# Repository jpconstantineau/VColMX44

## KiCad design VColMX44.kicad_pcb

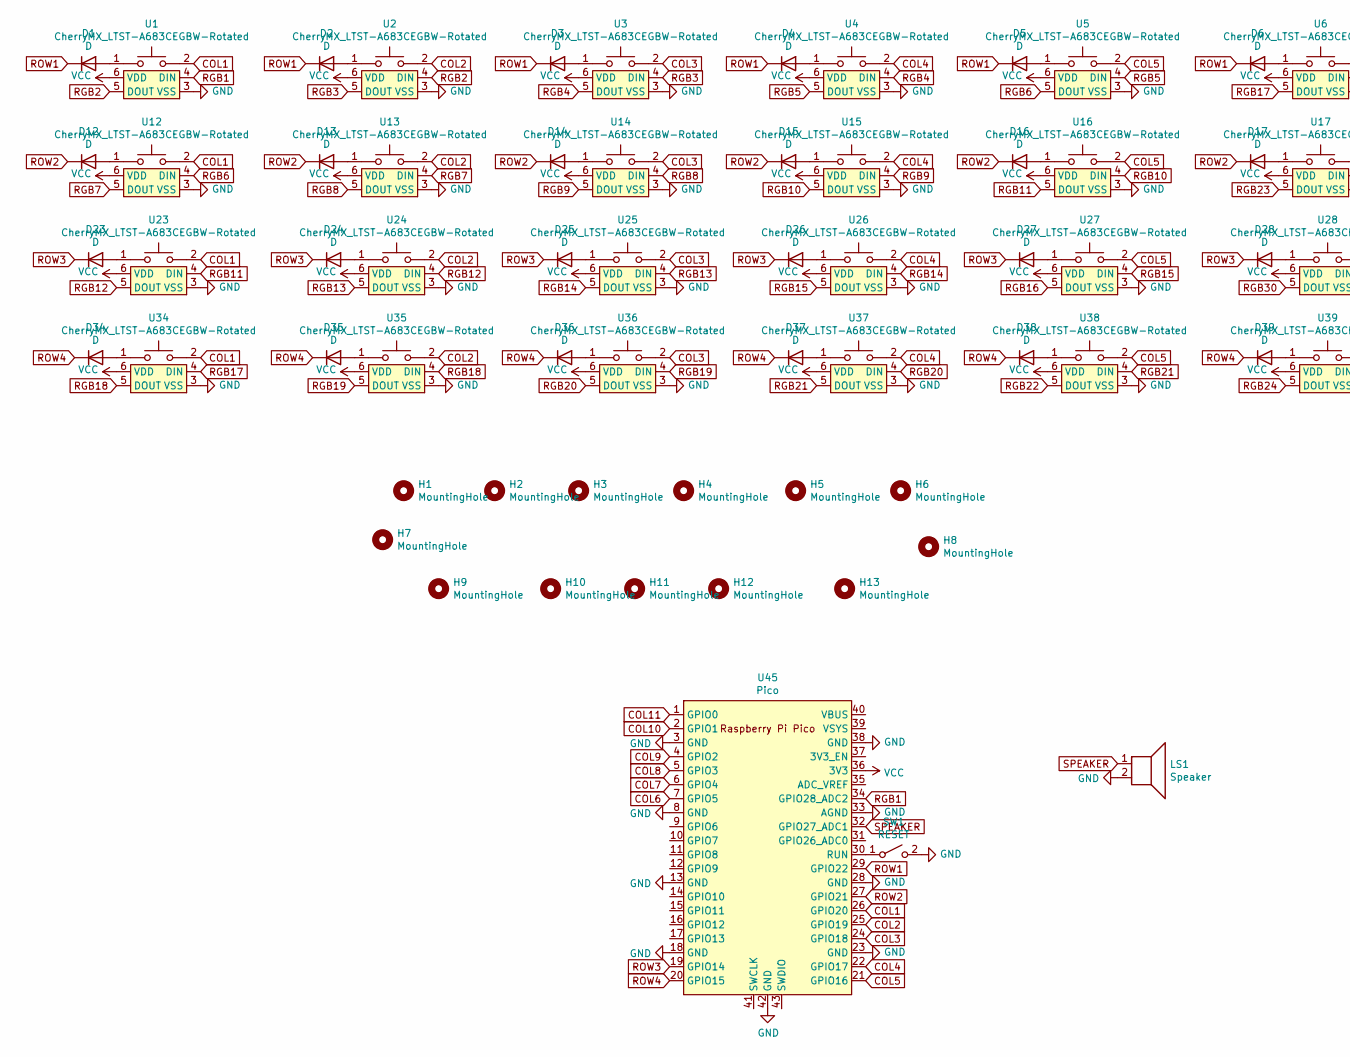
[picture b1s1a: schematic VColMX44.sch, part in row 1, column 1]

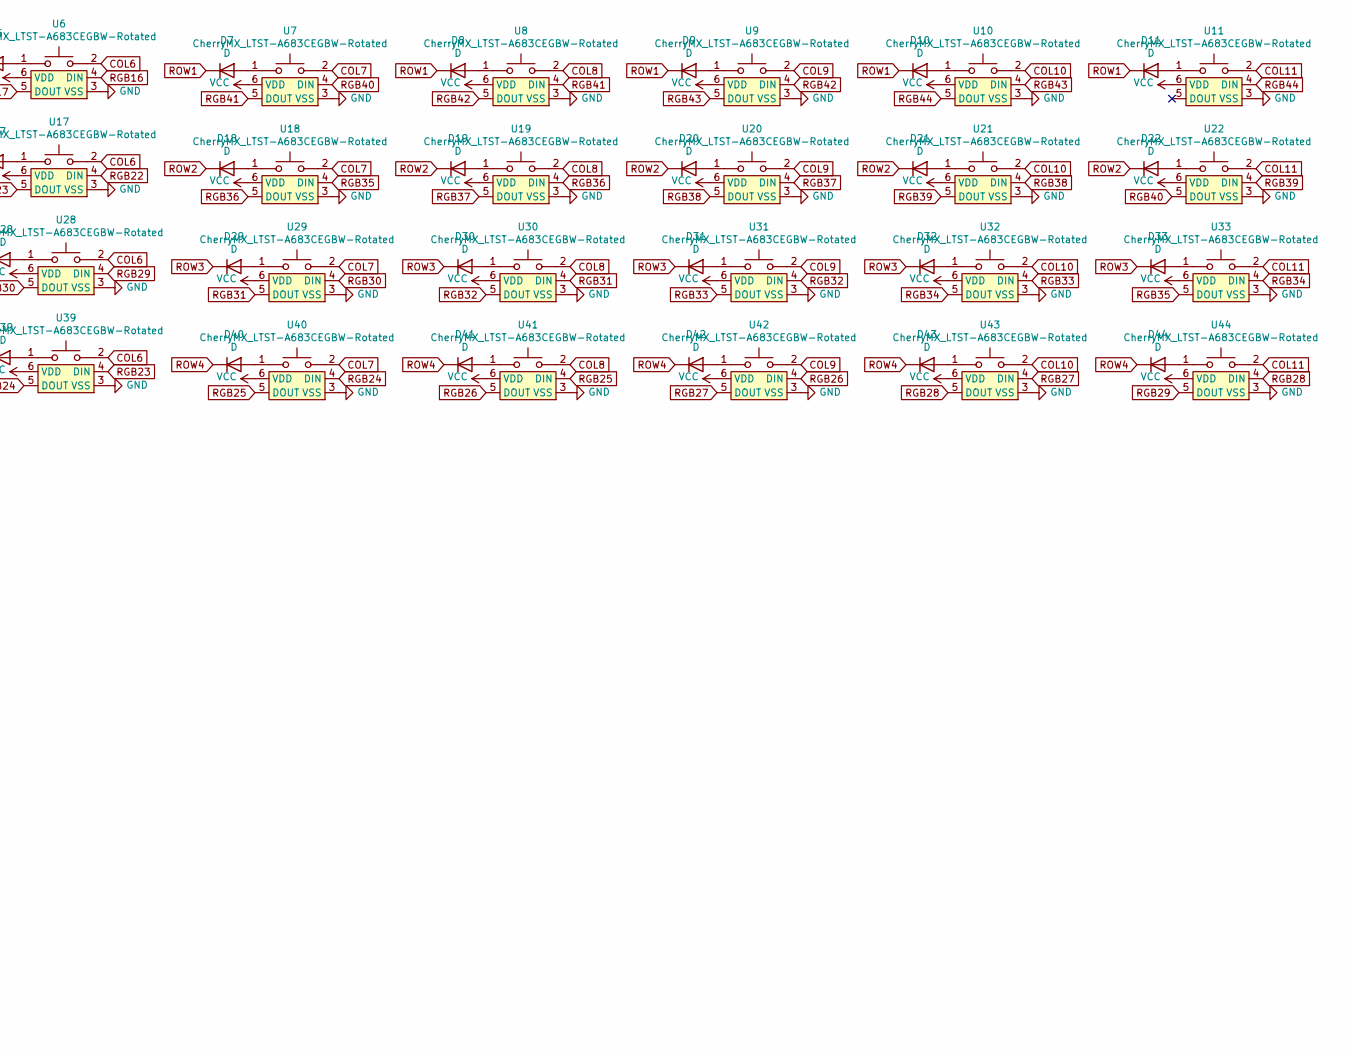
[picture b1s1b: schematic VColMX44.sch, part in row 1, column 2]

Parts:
D1, D2, D3, D4, D5, D6, D7, D8, D9, D10, D11, D12, D13, D14, D15, D16, D17, D18, D19, D20, D21, D22, D23, D24, D25, D26, D27, D28, D29, D30, D31, D32, D33, D34, D35, D36, D37, D38, D39, D40, D41, D42, D43, D44: D; D_SOD-123
H1, H2, H3, H4, H5, H6, H7, H8, H9, H10, H11, H12, H13: MountingHole; MountingHole_2.2mm_M2_DIN965
LS1: Speaker; Buzzer_Mallory_AST1109MLTRQ
SW1: RESET; SW_SPST_TL3342
U1, U2, U3, U4, U5, U6, U7, U8, U9, U10, U11, U12, U13, U14, U15, U16, U17, U18, U19, U20, U21, U22, U23, U24, U25, U26, U27, U28, U29, U30, U31, U32, U33, U34, U35, U36, U37, U38, U39, U40, U41, U42, U43, U44: CherryMX_LTST-A683CEGBW-Rotated; CherryMX_1.00u_PCB_KailhSocket_LTST-A683CEGBW-Rotated
U45: Pico; RPi_Pico_SMD

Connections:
COL1: U1.2, U12.2, U23.2, U34.2, U45.26 (GPIO20)
COL2: U2.2, U13.2, U24.2, U35.2, U45.25 (GPIO19)
COL3: U3.2, U14.2, U25.2, U36.2, U45.24 (GPIO18)
COL4: U4.2, U15.2, U26.2, U37.2, U45.22 (GPIO17)
COL5: U5.2, U16.2, U27.2, U38.2, U45.21 (GPIO16)
COL6: U6.2, U17.2, U28.2, U39.2, U45.7 (GPIO5)
COL7: U7.2, U18.2, U29.2, U40.2, U45.6 (GPIO4)
COL8: U8.2, U19.2, U30.2, U41.2, U45.5 (GPIO3)
COL9: U9.2, U20.2, U31.2, U42.2, U45.4 (GPIO2)
COL10: U10.2, U21.2, U32.2, U43.2, U45.2 (GPIO1)
COL11: U11.2, U22.2, U33.2, U44.2, U45.1 (GPIO0)
GND: LS1.2, SW1.2 (B), U1.3 (VSS), U2.3 (VSS), U3.3 (VSS), U4.3 (VSS), U5.3 (VSS), U6.3 (VSS), U7.3 (VSS), U8.3 (VSS), U9.3 (VSS), U10.3 (VSS), U11.3 (VSS), U12.3 (VSS), U13.3 (VSS), U14.3 (VSS), U15.3 (VSS), U16.3 (VSS), U17.3 (VSS), U18.3 (VSS), U19.3 (VSS), U20.3 (VSS), U21.3 (VSS), U22.3 (VSS), U23.3 (VSS), U24.3 (VSS), U25.3 (VSS), U26.3 (VSS), U27.3 (VSS), U28.3 (VSS), U29.3 (VSS), U30.3 (VSS), U31.3 (VSS), U32.3 (VSS), U33.3 (VSS), U34.3 (VSS), U35.3 (VSS), U36.3 (VSS), U37.3 (VSS), U38.3 (VSS), U39.3 (VSS), U40.3 (VSS), U41.3 (VSS), U42.3 (VSS), U43.3 (VSS), U44.3 (VSS), U45.3 (GND), U45.8 (GND), U45.13 (GND), U45.18 (GND), U45.23 (GND), U45.28 (GND), U45.33 (AGND), U45.38 (GND), U45.42 (GND)
unnamed: D1.2 (A), U1.1
unnamed: D2.2 (A), U2.1
unnamed: D3.2 (A), U3.1
unnamed: D4.2 (A), U4.1
unnamed: D5.2 (A), U5.1
unnamed: D6.2 (A), U6.1
unnamed: D7.2 (A), U7.1
unnamed: D8.2 (A), U8.1
unnamed: D9.2 (A), U9.1
unnamed: D10.2 (A), U10.1
unnamed: D11.2 (A), U11.1
unnamed: D12.2 (A), U12.1
unnamed: D13.2 (A), U13.1
unnamed: D14.2 (A), U14.1
unnamed: D15.2 (A), U15.1
unnamed: D16.2 (A), U16.1
unnamed: D17.2 (A), U17.1
unnamed: D18.2 (A), U18.1
unnamed: D19.2 (A), U19.1
unnamed: D20.2 (A), U20.1
unnamed: D21.2 (A), U21.1
unnamed: D22.2 (A), U22.1
unnamed: D23.2 (A), U23.1
unnamed: D24.2 (A), U24.1
unnamed: D25.2 (A), U25.1
unnamed: D26.2 (A), U26.1
unnamed: D27.2 (A), U27.1
unnamed: D28.2 (A), U28.1
unnamed: D29.2 (A), U29.1
unnamed: D30.2 (A), U30.1
unnamed: D31.2 (A), U31.1
unnamed: D32.2 (A), U32.1
unnamed: D33.2 (A), U33.1
unnamed: D34.2 (A), U34.1
unnamed: D35.2 (A), U35.1
unnamed: D36.2 (A), U36.1
unnamed: D37.2 (A), U37.1
unnamed: D38.2 (A), U38.1
unnamed: D39.2 (A), U39.1
unnamed: D40.2 (A), U40.1
unnamed: D41.2 (A), U41.1
unnamed: D42.2 (A), U42.1
unnamed: D43.2 (A), U43.1
unnamed: D44.2 (A), U44.1
unnamed: SW1.1 (A), U45.30 (RUN)
RGB1: U1.4 (DIN), U45.34 (GPIO28_ADC2)
RGB2: U1.5 (DOUT), U2.4 (DIN)
RGB3: U2.5 (DOUT), U3.4 (DIN)
RGB4: U3.5 (DOUT), U4.4 (DIN)
RGB5: U4.5 (DOUT), U5.4 (DIN)
RGB6: U5.5 (DOUT), U12.4 (DIN)
RGB7: U12.5 (DOUT), U13.4 (DIN)
RGB8: U13.5 (DOUT), U14.4 (DIN)
RGB9: U14.5 (DOUT), U15.4 (DIN)
RGB10: U15.5 (DOUT), U16.4 (DIN)
RGB11: U16.5 (DOUT), U23.4 (DIN)
RGB12: U23.5 (DOUT), U24.4 (DIN)
RGB13: U24.5 (DOUT), U25.4 (DIN)
RGB14: U25.5 (DOUT), U26.4 (DIN)
RGB15: U26.5 (DOUT), U27.4 (DIN)
RGB16: U6.4 (DIN), U27.5 (DOUT)
RGB17: U6.5 (DOUT), U34.4 (DIN)
RGB18: U34.5 (DOUT), U35.4 (DIN)
RGB19: U35.5 (DOUT), U36.4 (DIN)
RGB20: U36.5 (DOUT), U37.4 (DIN)
RGB21: U37.5 (DOUT), U38.4 (DIN)
RGB22: U17.4 (DIN), U38.5 (DOUT)
RGB23: U17.5 (DOUT), U39.4 (DIN)
RGB24: U39.5 (DOUT), U40.4 (DIN)
RGB25: U40.5 (DOUT), U41.4 (DIN)
RGB26: U41.5 (DOUT), U42.4 (DIN)
RGB27: U42.5 (DOUT), U43.4 (DIN)
RGB28: U43.5 (DOUT), U44.4 (DIN)
RGB29: U28.4 (DIN), U44.5 (DOUT)
RGB30: U28.5 (DOUT), U29.4 (DIN)
RGB31: U29.5 (DOUT), U30.4 (DIN)
RGB32: U30.5 (DOUT), U31.4 (DIN)
RGB33: U31.5 (DOUT), U32.4 (DIN)
RGB34: U32.5 (DOUT), U33.4 (DIN)
RGB35: U18.4 (DIN), U33.5 (DOUT)
RGB36: U18.5 (DOUT), U19.4 (DIN)
RGB37: U19.5 (DOUT), U20.4 (DIN)
RGB38: U20.5 (DOUT), U21.4 (DIN)
RGB39: U21.5 (DOUT), U22.4 (DIN)
RGB40: U7.4 (DIN), U22.5 (DOUT)
RGB41: U7.5 (DOUT), U8.4 (DIN)
RGB42: U8.5 (DOUT), U9.4 (DIN)
RGB43: U9.5 (DOUT), U10.4 (DIN)
RGB44: U10.5 (DOUT), U11.4 (DIN)
ROW1: D1.1 (K), D2.1 (K), D3.1 (K), D4.1 (K), D5.1 (K), D6.1 (K), D7.1 (K), D8.1 (K), D9.1 (K), D10.1 (K), D11.1 (K), U45.29 (GPIO22)
ROW2: D12.1 (K), D13.1 (K), D14.1 (K), D15.1 (K), D16.1 (K), D17.1 (K), D18.1 (K), D19.1 (K), D20.1 (K), D21.1 (K), D22.1 (K), U45.27 (GPIO21)
ROW3: D23.1 (K), D24.1 (K), D25.1 (K), D26.1 (K), D27.1 (K), D28.1 (K), D29.1 (K), D30.1 (K), D31.1 (K), D32.1 (K), D33.1 (K), U45.19 (GPIO14)
ROW4: D34.1 (K), D35.1 (K), D36.1 (K), D37.1 (K), D38.1 (K), D39.1 (K), D40.1 (K), D41.1 (K), D42.1 (K), D43.1 (K), D44.1 (K), U45.20 (GPIO15)
SPEAKER: LS1.1, U45.32 (GPIO27_ADC1)
VCC: U1.6 (VDD), U2.6 (VDD), U3.6 (VDD), U4.6 (VDD), U5.6 (VDD), U6.6 (VDD), U7.6 (VDD), U8.6 (VDD), U9.6 (VDD), U10.6 (VDD), U11.6 (VDD), U12.6 (VDD), U13.6 (VDD), U14.6 (VDD), U15.6 (VDD), U16.6 (VDD), U17.6 (VDD), U18.6 (VDD), U19.6 (VDD), U20.6 (VDD), U21.6 (VDD), U22.6 (VDD), U23.6 (VDD), U24.6 (VDD), U25.6 (VDD), U26.6 (VDD), U27.6 (VDD), U28.6 (VDD), U29.6 (VDD), U30.6 (VDD), U31.6 (VDD), U32.6 (VDD), U33.6 (VDD), U34.6 (VDD), U35.6 (VDD), U36.6 (VDD), U37.6 (VDD), U38.6 (VDD), U39.6 (VDD), U40.6 (VDD), U41.6 (VDD), U42.6 (VDD), U43.6 (VDD), U44.6 (VDD), U45.36 (3V3)

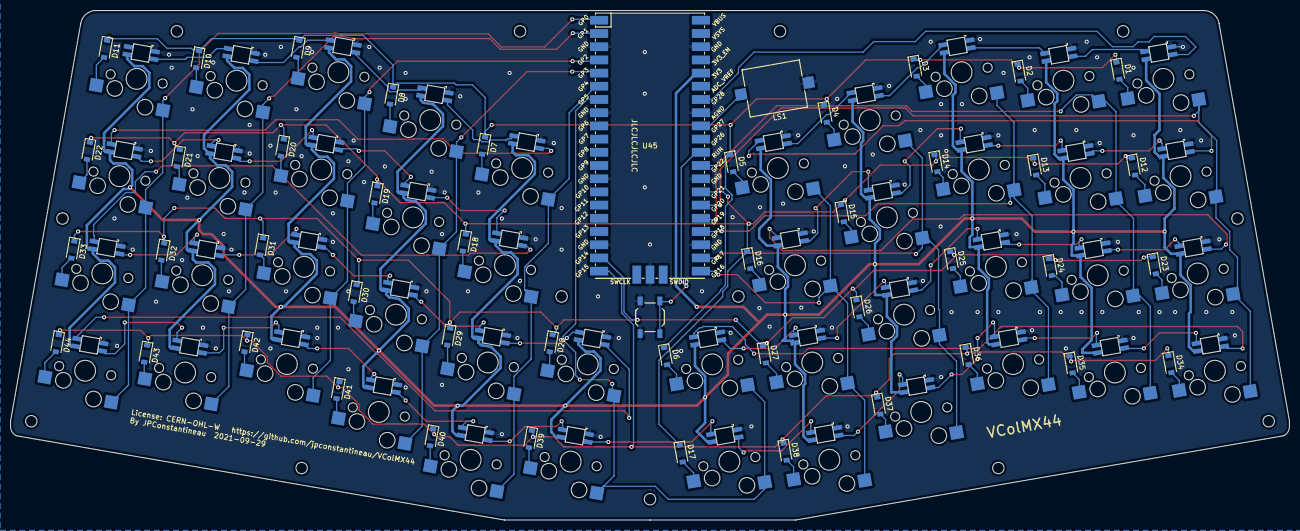
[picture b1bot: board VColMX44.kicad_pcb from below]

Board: 2 copper layers, 246.0 x 98.0 mm, 104 parts (47 on the bottom side), 107 nets.

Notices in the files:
VColMX44.kicad_pcb:
License: CERN-OHL-W https://github.com/jpconstantineau/VColMX44
